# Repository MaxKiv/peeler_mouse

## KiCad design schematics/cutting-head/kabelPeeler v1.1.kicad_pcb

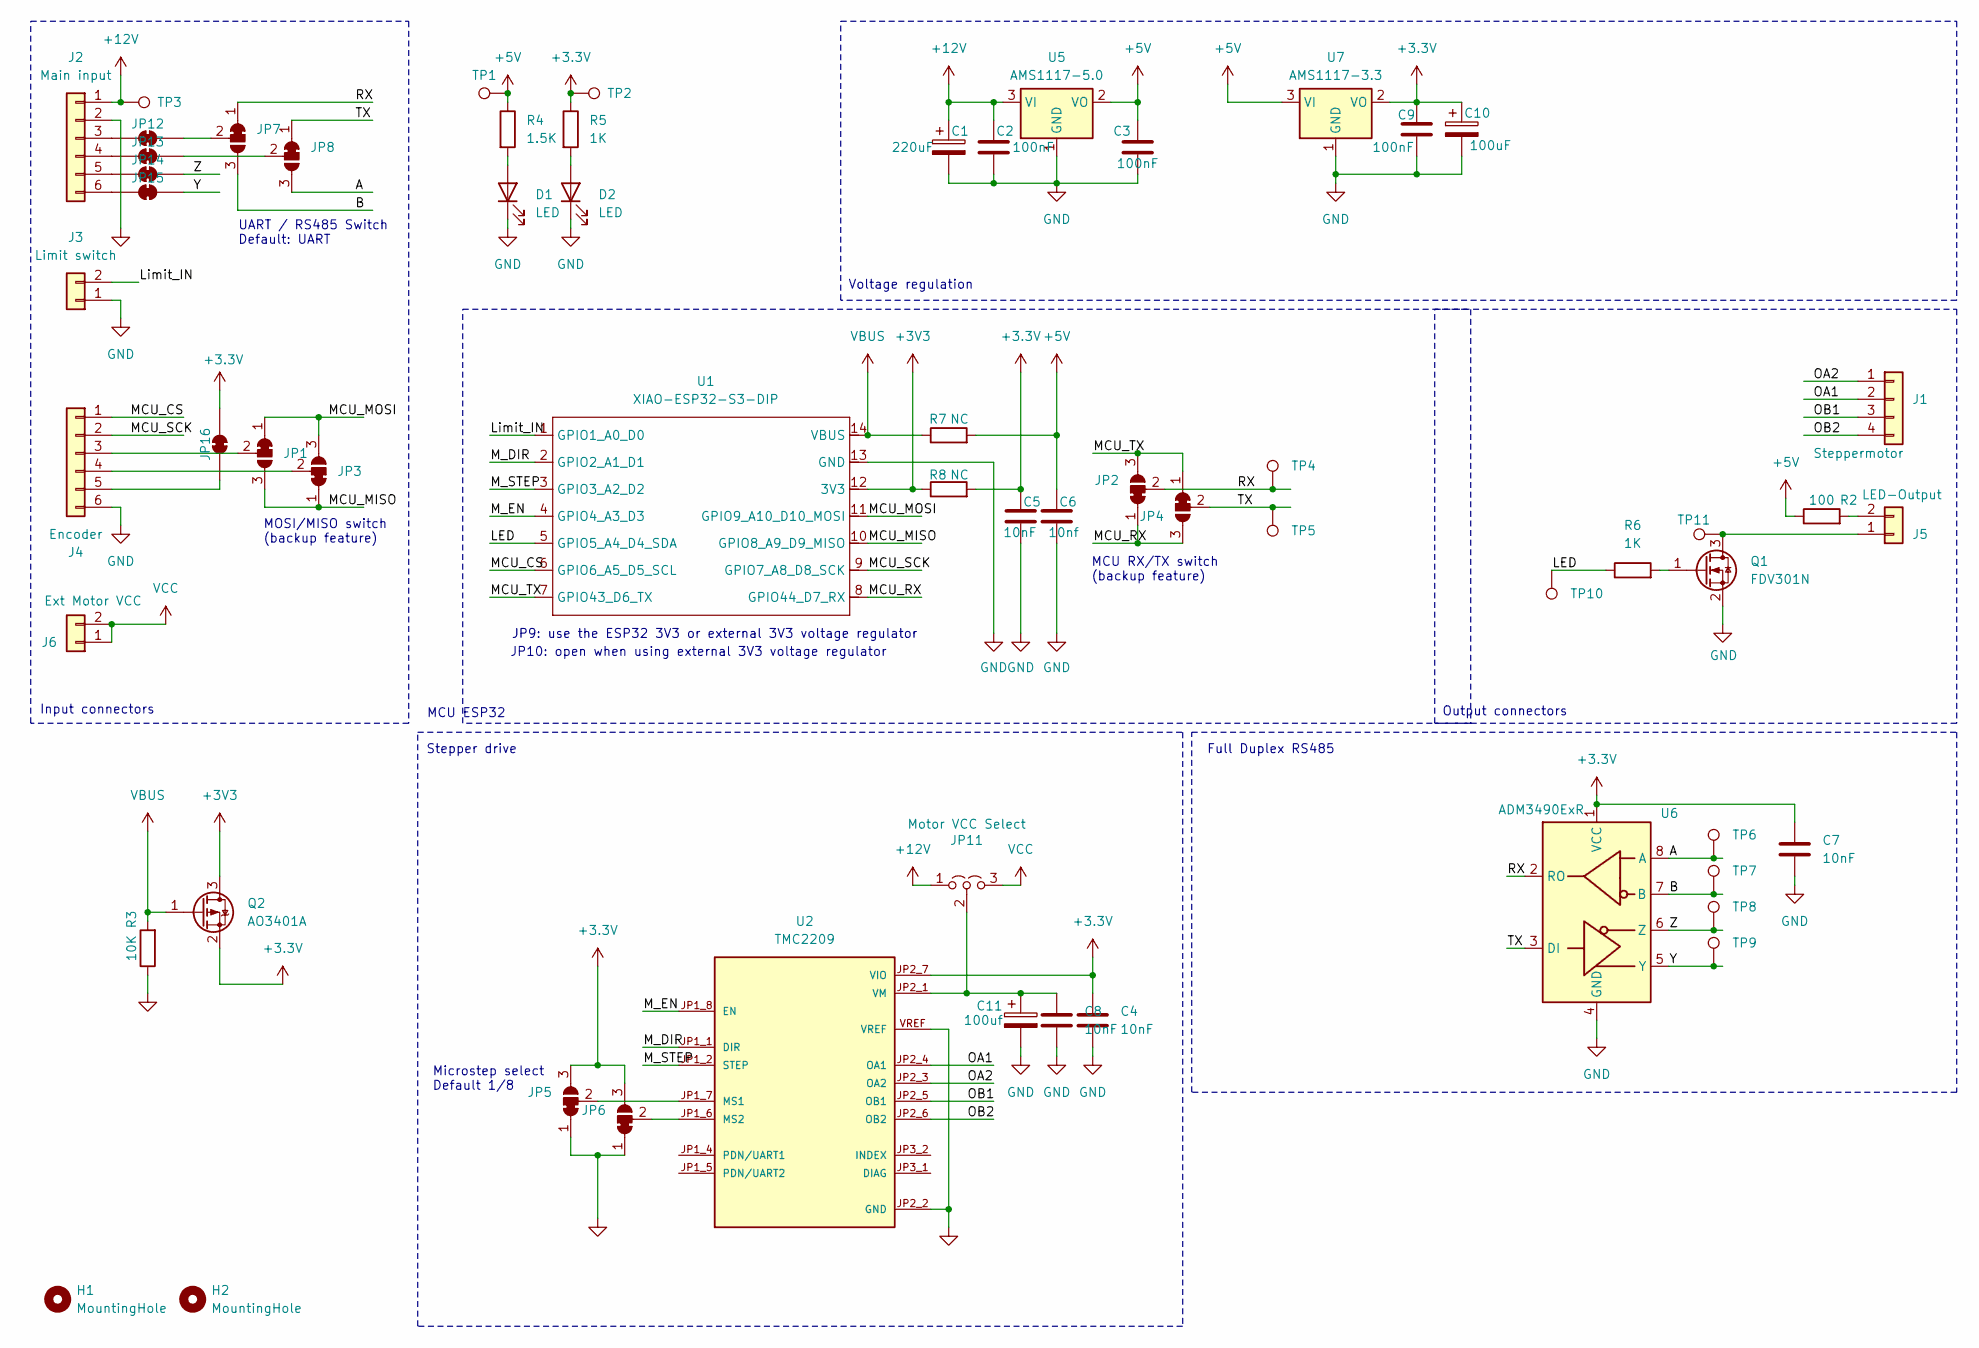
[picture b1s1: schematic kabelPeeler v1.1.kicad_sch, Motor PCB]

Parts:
C1: 220uF; CP_Radial_D8.0mm_P3.50mm
C2, C3, C9: 100nF; C_0805_2012Metric_Pad1.18x1.45mm_HandSolder
C4, C5, C7, C8: 10nF; C_0805_2012Metric_Pad1.18x1.45mm_HandSolder
C6: 10nf; C_0805_2012Metric_Pad1.18x1.45mm_HandSolder
C10: 100uF; CP_Radial_D5.0mm_P2.00mm
C11: 100uf; CP_Radial_D5.0mm_P2.00mm
D1, D2: LED; LED_0805_2012Metric_Pad1.15x1.40mm_HandSolder
H1, H2: MountingHole; MountingHole_2.2mm_M2_DIN965
J1: Steppermotor; JST_XH_B4B-XH-A_1x04_P2.50mm_Vertical
J2: Main input; JST_XH_B6B-XH-A_1x06_P2.50mm_Vertical
J3: Limit switch; JST_XH_B2B-XH-A_1x02_P2.50mm_Vertical
J4: Encoder; JST_XH_B6B-XH-A_1x06_P2.50mm_Vertical
J5: LED-Output; JST_XH_B2B-XH-A_1x02_P2.50mm_Vertical
J6: Ext Motor VCC; JST_XH_B2B-XH-A_1x02_P2.50mm_Vertical
JP1, JP3: MOSI/MISO; SolderJumper-3_P1.3mm_Bridged12_RoundedPad1.0x1.5mm
JP2, JP4: RX/TX Swap; SolderJumper-3_P1.3mm_Bridged12_RoundedPad1.0x1.5mm
JP5: MS1 select; SolderJumper-3_P1.3mm_Bridged12_RoundedPad1.0x1.5mm
JP6: MS2 select; SolderJumper-3_P1.3mm_Bridged12_RoundedPad1.0x1.5mm
JP7, JP8: SolderJumper_3_Bridged12; SolderJumper-3_P1.3mm_Bridged12_RoundedPad1.0x1.5mm
JP11: Motor VCC Select; PinHeader_1x03_P2.54mm_Vertical
JP12, JP13, JP14, JP15, JP16: SolderJumper_2_Bridged; SolderJumper-2_P1.3mm_Bridged_RoundedPad1.0x1.5mm
Q1: FDV301N; SOT-23_Handsoldering
Q2: AO3401A; SOT-23
R2: 100; R_0805_2012Metric_Pad1.20x1.40mm_HandSolder
R3: 10K; R_0805_2012Metric_Pad1.20x1.40mm_HandSolder
R4: 1.5K; R_0805_2012Metric_Pad1.20x1.40mm_HandSolder
R5, R6: 1K; R_0805_2012Metric_Pad1.20x1.40mm_HandSolder
R7, R8: NC; R_0805_2012Metric_Pad1.20x1.40mm_HandSolder
TP1, TP2, TP3, TP4, TP5, TP6, TP7, TP8, TP9, TP10, TP11: TestPoint; TestPoint_Pad_D1.0mm
U1: XIAO-ESP32-S3-DIP
U2: TMC2209; MODULE_TMC2208_SILENTSTEPSTICK
U5: AMS1117-5.0; SOT-223-3_TabPin2
U6: ADM3490ExR; SOIC-8_3.9x4.9mm_P1.27mm
U7: AMS1117-3.3; SOT-223-3_TabPin2

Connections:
+3.3V: C4.1, C5.1, C7.1, C9.1, C10.1, JP5.3 (B), JP6.3 (B), JP16.2 (B), Q2.2 (S), R5.1, R8.2, TP2.1 (1_1), U2.JP2_7 (VIO), U6.1 (VCC), U7.2 (VO)
+3V3: Q2.3 (D), R8.1, U1.12 (3V3)
+5V: C3.1, C6.1, R2.1, R4.1, R7.2, TP1.1 (1_1), U5.2 (VO), U7.3 (VI)
+12V: C1.1, C2.1, J2.1, JP11.1 (A), TP3.1 (1_1), U5.3 (VI)
/A: JP8.3 (B), TP6.1, U6.8 (A)
/B: JP7.3 (B), TP7.1, U6.7 (B)
/LED: R6.1, TP10.1 (1_1), U1.5 (GPIO5_A4_D4_SDA)
/Limit_IN: J3.2, U1.1 (GPIO1_A0_D0)
/MCU_CS: J4.1, U1.6 (GPIO6_A5_D5_SCL)
/MCU_MISO: JP1.3 (B), JP3.1 (A), U1.10 (GPIO8_A9_D9_MISO)
/MCU_MOSI: JP1.1 (A), JP3.3 (B), U1.11 (GPIO9_A10_D10_MOSI)
/MCU_RX: JP2.1 (A), JP4.3 (B), U1.8 (GPIO44_D7_RX)
/MCU_SCK: J4.2, U1.9 (GPIO7_A8_D8_SCK)
/MCU_TX: JP2.3 (B), JP4.1 (A), U1.7 (GPIO43_D6_TX)
/M_DIR: U1.2 (GPIO2_A1_D1), U2.JP1_1 (DIR)
/M_EN: U1.4 (GPIO4_A3_D3), U2.JP1_8 (EN)
/M_STEP: U1.3 (GPIO3_A2_D2), U2.JP1_2 (STEP)
/OA1: J1.2, U2.JP2_4 (OA1)
/OA2: J1.1, U2.JP2_3 (OA2)
/OB1: J1.3, U2.JP2_5 (OB1)
/OB2: J1.4, U2.JP2_6 (OB2)
/RX: JP2.2 (C), JP7.1 (A), TP4.1 (1_1), U6.2 (RO)
/TX: JP4.2 (C), JP8.1 (A), TP5.1 (1_1), U6.3 (DI)
/Y: JP15.2 (B), TP9.1, U6.5 (Y)
/Z: JP14.2 (B), TP8.1, U6.6 (Z)
GND: C1.2, C2.2, C3.2, C4.2, C5.2, C6.2, C7.2, C8.2, C9.2, C10.2, C11.2, D1.1 (K), D2.1 (K), J2.2, J3.1, J4.6, JP5.1 (A), JP6.1 (A), Q1.2 (S), R3.1, U1.13 (GND), U2.JP2_2 (GND), U2.JP2_8 (GND), U2.VREF, U5.1 (GND), U6.4 (GND), U7.1 (GND)
unnamed: D1.2 (A), R4.2
unnamed: D2.2 (A), R5.2
unnamed: J2.3, JP12.1 (A)
unnamed: J2.4, JP13.1 (A)
unnamed: J2.5, JP14.1 (A)
unnamed: J2.6, JP15.1 (A)
unnamed: J4.3, JP1.2 (C)
unnamed: J4.4, JP3.2 (C)
unnamed: J4.5, JP16.1 (A)
unnamed: J5.1, Q1.3 (D), TP11.1 (1_1)
unnamed: J5.2, R2.2
unnamed: JP5.2 (C), U2.JP1_7 (MS1)
unnamed: JP6.2 (C), U2.JP1_6 (MS2)
unnamed: C8.1, C11.1, JP11.2 (C), U2.JP2_1 (VM)
unnamed: JP7.2 (C), JP12.2 (B)
unnamed: JP8.2 (C), JP13.2 (B)
unnamed: Q1.1 (G), R6.2
VBUS: Q2.1 (G), R3.2, R7.1, U1.14 (VBUS)
VCC: J6.1, J6.2, JP11.3 (B)

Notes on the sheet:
Full Duplex RS485
MCU ESP32
Voltage regulation
Microstep select Default 1/8
JP10: open when using external 3V3 voltage regulator
Stepper drive
Output connectors
UART / RS485 Switch Default: UART
MCU RX/TX switch (backup feature)
JP9: use the ESP32 3V3 or external 3V3 voltage regulator
Input connectors
MOSI/MISO switch (backup feature)

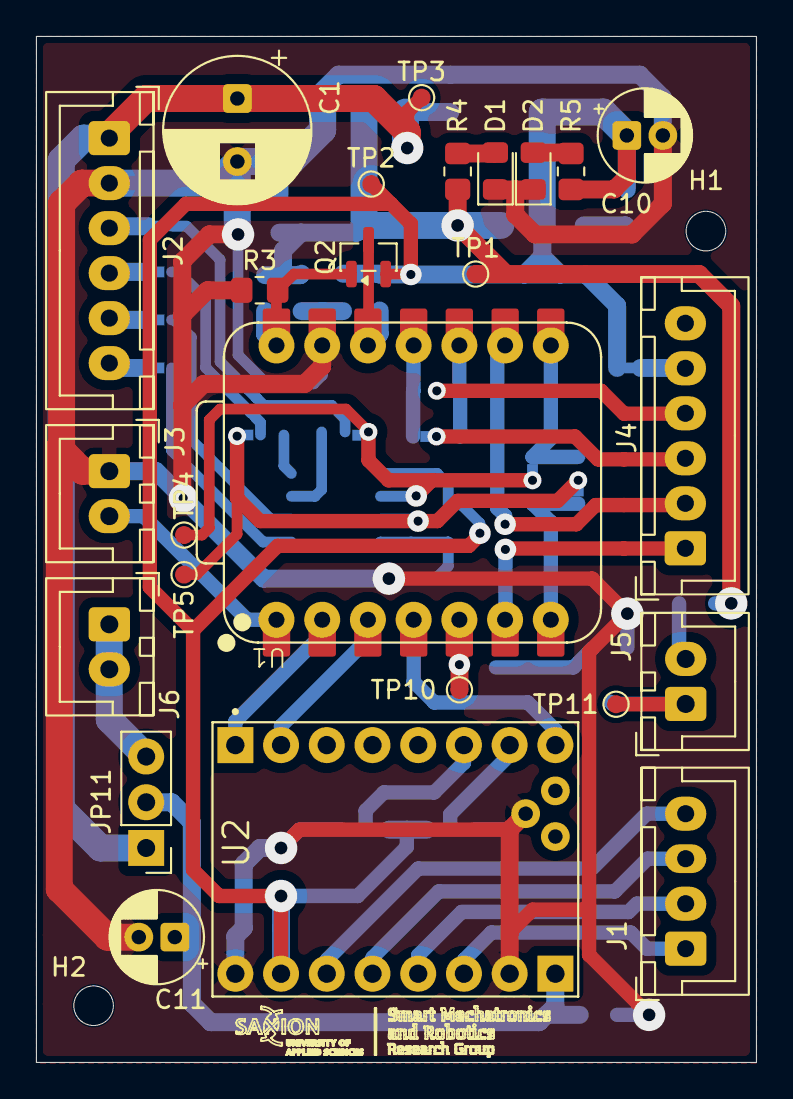
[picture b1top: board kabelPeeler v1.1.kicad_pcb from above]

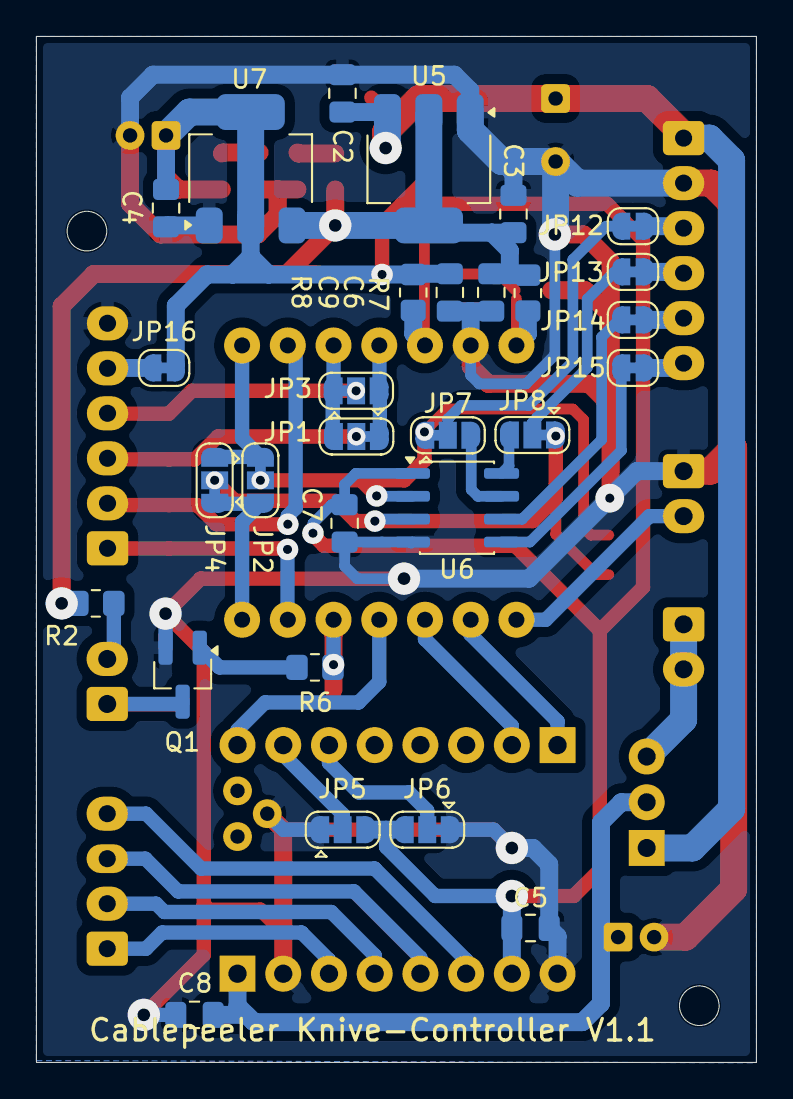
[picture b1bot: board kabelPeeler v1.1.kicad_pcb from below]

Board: 2 copper layers, 40.0 x 57.0 mm, 56 parts (29 on the bottom side), 45 nets.

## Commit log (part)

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2025-09-01 feat(schematic): first draft of peeler mouse prototype schematic
2025-09-10 feat(resources): Saving other esp32 repo's as reference
2025-09-10 feat(resources): add flash instructions
2025-09-11 chore: fighting git submodules
2025-09-11 feat(esp32): first draft of webserver with camera stream
2025-09-12 feat(esp32): refactor into server/wifi/blink tasks
2025-09-17 feat(control): added control task, added ability to set setpoints from webpage
2025-09-18 feat(servo): adding in pwm drivers, although this one seems quite shit
2025-09-18 wip: figuring out why i get ledc errors when i set a nonzero pwm value for the 2nd time
2025-11-04 feat(esp32s3): first draft esp32s3 toolchain
2025-11-04 chore: organisation, documentation
2025-11-04 wip(esp32s3): WIP toolchain
2025-11-06 feat(stm32h7): basic tooling + blinky
2025-11-06 feat(stm32h7): running basic ethernet example!
2025-11-10 feat(stm32h7): button + lcd task
2025-11-11 feat(stm32h7): finished lcd driver
2025-11-13 feat(stm32h7): tb6600 stepper driver
2025-11-13 feat(stm32h7): inter task comms
2025-11-13 wip: test motor and discover embedded-graphics is blocking...
2025-11-24 feat(tb6600): simple tb6600 stepper driver
2025-11-24 wip(showcase):
2025-11-24 feat(showcase): latched motor movement
2025-11-25 feat(pot): pot driver + showcase & tb6600 fixes
2025-12-03 feat(tb6600): hardware pwm + maxon draft
2025-12-08 chore: gather datasheets
2025-12-10 feat(l9110): working L9110 driver
2025-12-17 feat(stage-1): working stage-1 firmware + as5048 wip driver
2026-01-13 feat(quadrature_encoder): driver
2026-01-14 wip(supervisor): first draft of new supervisor to connect hmi <-> motors
2026-01-15 feat(hmi): updated LCD to new appstate structure
2026-01-16 wip(integration)
2026-02-04 feat(esp32s3): set up toolchain and env for esp32s3
2026-02-06 chore: organising
2026-02-06 feat(esp32s3-idf): esp32s3-idf toolchain setup
2026-02-06 fix: downgrade idf
2026-02-10 wip: draft of new structure
2026-02-10 fix: properly include esp32-camera submodule
2026-02-10 feat: SD card writing, server displays PGM images, facing tearing issues
2026-02-13 feat(sd): restructure + move SD card logging to seperate task
2026-02-13 fix: sync framebuffer using watch instead of signals
2026-02-19 feat(messenger): messenger lib v0.0.1
2026-02-19 feat(esp32s3): uart comms + framing, controller setup, camera fps
2026-02-20 feat(messenger): v0.0.2
2026-02-20 feat(l9110): add l9110 driver for esp32
2026-02-20 feat(control): Add control loop and motor/led actuation
2026-02-20 chore: cargo clippy run
2026-02-20 fix(l9110): remove defmt dependencies from l9110
2026-02-20 feat(vision): added simple average and 3x3 horizontal edge detection kernels
2026-02-26 chore: docs
2026-03-12 wip(stm32): UART setpoint/report comms, tasks done, commsperiph TODO
2026-03-12 wip: encoder on stm32
2026-03-12 Revert "wip: encoder on stm32"
    This reverts commit 860c732abaadc12611d79aefc24b07ef2b3f0aaf.
2026-03-12 feat(messenger_mouse): v0.0.2
2026-03-12 wip(esp32): control loop + reporting
2026-03-13 wip(esp32): added jpeg streaming flag, disfunctional
2026-03-13 chore: remove esp32-camera annotations, update messenger mouse
2026-03-13 chore: parameter tweaking + prints
2026-03-13 chore: collect esp32s3 data
2026-03-18 feat(esp32): as5048 encoder task working
2026-03-18 feat(v0.1.0): added Knife/Encoder related logic
2026-03-18 wip: towards new motorcontroller structure
2026-03-18 wip: motor controller
2026-03-18 feat(l9110): improved api
2026-03-19 wip: tmc22208 steppper esp
2026-03-20 wip: stepper driver + limit switch + motor control task
2026-03-24 feat(rmt_stepper): Try out RMT stepper driver
2026-03-24 feat(stm32): hmi v2.0
2026-03-24 fix(messenger_mouse): add defmt derives
2026-03-24 wip(esp32): tweak motor accel
2026-03-25 wip: awaiting huge message lib refactor
2026-03-25 wip: huge hmi/ message lib / controller refactor
2026-03-25 wip: refactor
2026-03-26 chore: update readme
2026-03-31 feat(stm): hmi + supervisor + motorcommand refactor
2026-03-31 wip(esp): proper stepper controller
2026-03-31 fix(stm32): comms fix
2026-04-07 wip: motor controller refactor, limit switch functionality
2026-04-08 chore: stop tracking embuild dir
2026-04-08 feat(embed): cargo embed config
2026-04-08 wip(esp32s3): camera framebuffer synchronisation refactor, stuck on stepper
2026-04-13 feat(esp32s3): improve async behavior, less logging
2026-04-13 fix: point to patched esp32-camera on bitbucket
2026-04-13 feat(esp32s3): stepper ramping
2026-04-13 feat(stm32): encoder improvements, hmi position mode fix
2026-04-13 wip: stepper ramping + propper dir
2026-04-13 w: low level stepper task -> seems finished? High level position control next
2026-04-14 chore: datasheet
2026-04-20 feat(esp32s3): stepper velocity + position mode
2026-04-21 wip: move to pcb
2026-04-23 feat: add pcb schematic
2026-04-24 feat: various integration fixes
2026-04-29 chore: make pin-out diagram
2026-04-29 feat(esp32): enable concurrent usage of controller & webserver
2026-04-29 chore(stm32): clearer names, add logging around comms
2026-04-30 fix(comms): fix esp32 -> stm32 comms writing abundant zeros
2026-04-30 wip: vision algo, todo: encoder, vision output visualisation, LED setup
2026-05-06 chore: update base station schematic
2026-05-13 feat(esp32s3): encoder stall monitoring & limit switch behavior
2026-05-19 chore: tweak led brightness
2026-05-19 feat: camera data script
2026-05-19 feat: cutting-head schematic v1.1
2026-05-20 feat(esp32s3): refactor encoder stall logic
2026-05-22 wip: encoder stall improvements
2026-05-27 fix: encoder improvements, fixed dir bug in rot/trans
2026-05-27 feat(esp32): blink boot indicator
2026-05-27 feat(stm32): led brightness constant
2026-05-27 wip: control effort rework, esp32 side done
2026-05-28 chore: remove workspace crates that test partial functionality for clarity
2026-05-28 feat(base-station): organisation, move to vision managed trans/rot motors
2026-05-29 feat(esp-master): stm32 now acts as slave when ControlMode::Vision
2026-06-09 feat(stm32): mousefood + ratatui HMI
2026-06-22 wip: webserver enhancements
2026-06-23 wip: vision algo upgrade
2026-06-29 chore: update schematics
2026-06-30 feat(algo): new vision algo, webserver now visualises
